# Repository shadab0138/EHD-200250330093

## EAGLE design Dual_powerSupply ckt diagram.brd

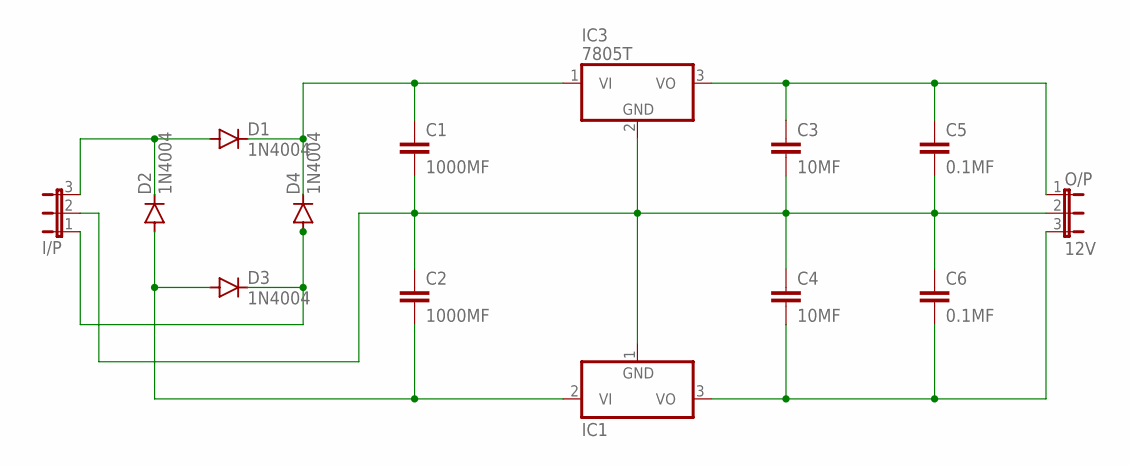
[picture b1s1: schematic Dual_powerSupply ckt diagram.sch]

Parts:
C1, C2: 1000MF; C2.5-3
C3, C4: 10MF; C2.5-3
C5, C6: 0.1MF; C2.5-3
D1, D2, D3, D4: 1N4004; DO41-10
I/P: JP2E; JP2
IC1: 7905T; TO220H
IC3: 7805T; TO220H
O/P: 12V; JP2

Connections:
unnamed: D1.A, D2.C, I/P.3
unnamed: C2.2, D2.A, D3.A, IC1.2 (VI)
unnamed: C1.2, C2.1, C3.2, C4.1, C5.2, C6.1, I/P.2, IC1.1 (GND), IC3.2 (GND), O/P.2
unnamed: C1.1, D1.C, D4.C, IC3.1 (VI)
unnamed: D3.C, D4.A, I/P.1
unnamed: C4.2, C6.2, IC1.3 (VO), O/P.3
unnamed: C3.1, C5.1, IC3.3 (VO), O/P.1

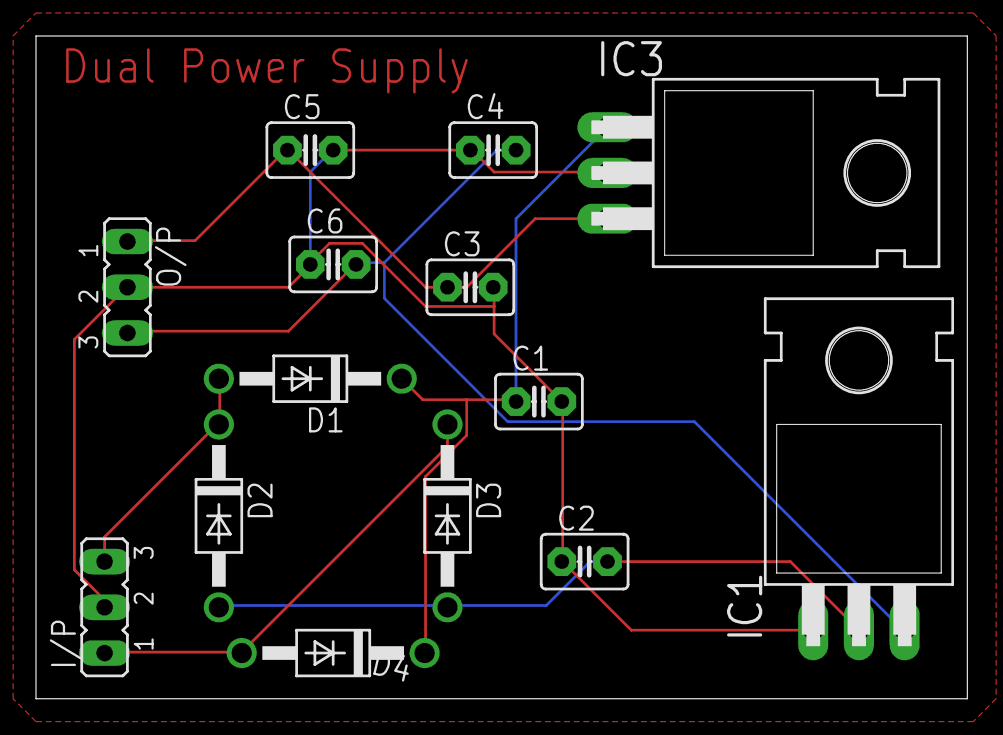
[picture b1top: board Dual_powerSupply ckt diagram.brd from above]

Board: 2 copper layers, 51.7 x 36.8 mm, 14 parts (0 on the bottom side), 7 nets.

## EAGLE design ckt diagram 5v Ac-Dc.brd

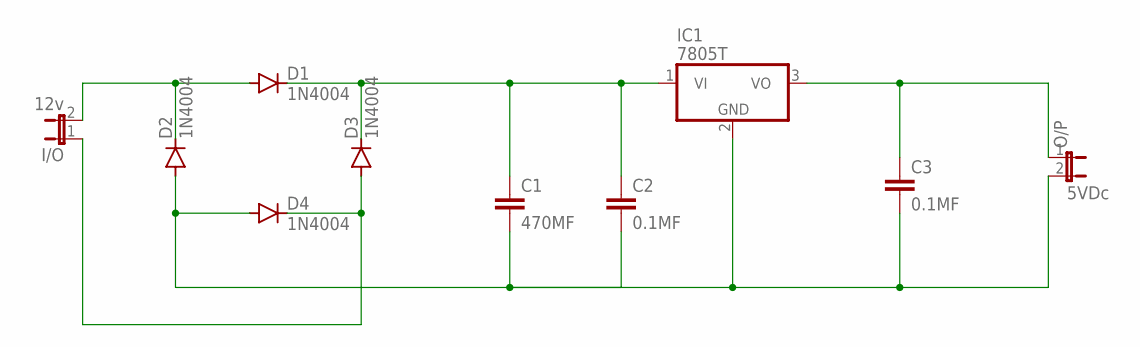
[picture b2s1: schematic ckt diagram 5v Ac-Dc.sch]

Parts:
C1: 470MF; C2.5-2
C2, C3: 0.1MF; C2.5-2
D1, D2, D3, D4: 1N4004; DO41-10
I/O: 12v; JP1
IC1: 7805T; TO220H
O/P: 5VDc; JP1

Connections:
unnamed: D1.A, D2.C, I/O.2
unnamed: C1.2, C2.2, C3.2, D2.A, D4.A, IC1.2 (GND), O/P.2
unnamed: D3.A, D4.C, I/O.1
unnamed: C1.1, C2.1, D1.C, D3.C, IC1.1 (VI)
unnamed: C3.1, IC1.3 (VO), O/P.1

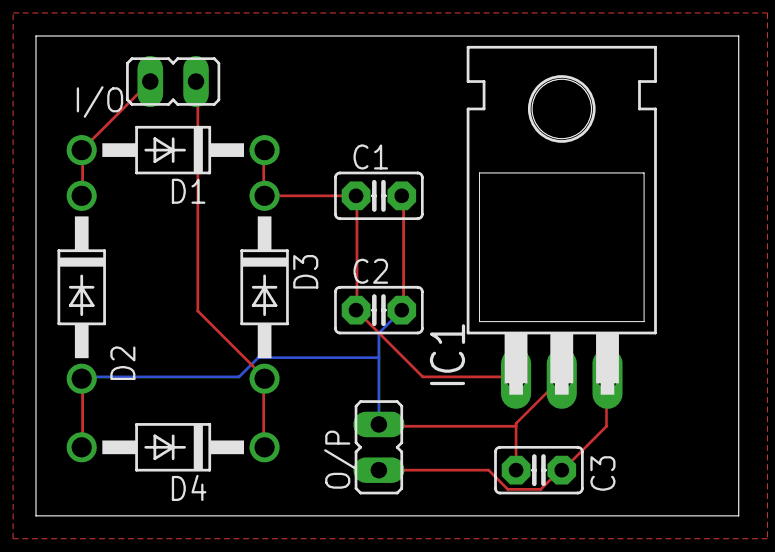
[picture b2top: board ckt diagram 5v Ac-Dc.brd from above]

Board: 2 copper layers, 39.0 x 26.7 mm, 10 parts (0 on the bottom side), 5 nets.
